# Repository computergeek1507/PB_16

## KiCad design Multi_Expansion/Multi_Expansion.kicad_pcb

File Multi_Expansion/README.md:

# Copyright and Disclaimer
Copyright: Scott Hanson

This documentation describes Open Hardware and is licensed under the CERN Open Hardware License Version 2 - Strongly Reciprocal. (CERN-OHL-S)

You may redistribute and modify this documentation under the terms of the CERN OHL-S-v2 (https://ohwr.org/cern_ohl_s_v2.txt). This documentation is distributed WITHOUT ANY EXPRESS OR IMPLIED WARRANTY, INCLUDING OF MERCHANTABILITY, SATISFACTORY QUALITY AND FITNESS FOR A PARTICULAR PURPOSE. Please see the CERN OHL v2-S for applicable conditions

**Under CERN OHL-S-v2, derivative work must be publicly released as defined in subsection 3.3**

# Multi Expansion

The Multi Expansion is a dual Differental Reciever output board with eight local pixel outputs for the PB16. It works with Smart and Dumb Differental Recievers. All the design files are open source and available on github.

## [Part BOM](https://github.com/computergeek1507/PB_16/raw/master/Multi_Expansion/Multi_Expansion.ods)

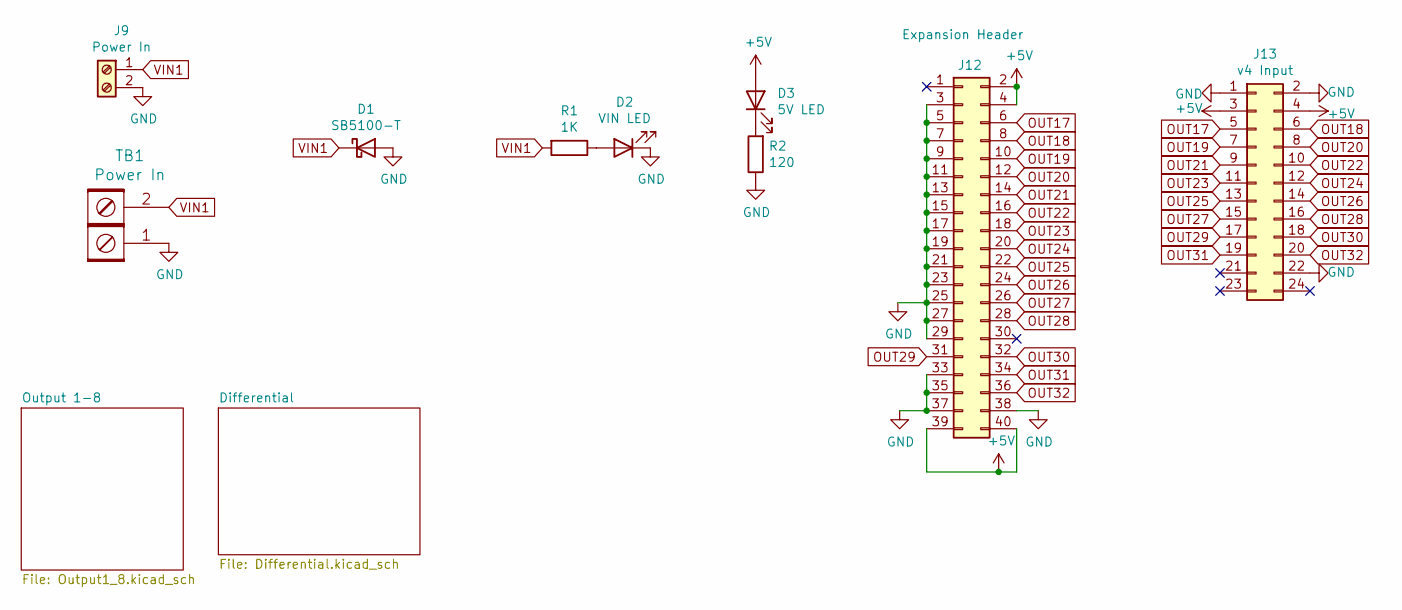
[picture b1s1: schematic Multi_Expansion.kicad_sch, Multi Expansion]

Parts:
D1: SB5100-T; D_DO-201AD_P12.70mm_Horizontal; MPN SB5100-T; Digi-Key_PN SB5100DICT-ND
D2: VIN LED; LED_D3.0mm_Clear; MPN WP3A8GD; Digi-Key_PN 754-1217-ND
D3: 5V LED; LED_D3.0mm_Clear; MPN WP3A8GD; Digi-Key_PN 754-1217-ND
J9: Power In; TerminalBlock_MetzConnect_Type701_RT11L02HGLU_1x02_P6.35mm_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; Digi-Key_PN ED2675-ND
J12: Expansion Header; IDC-Header_2x20_P2.54mm_Vertical; MPN SBH11-PBPC-D20-ST-BK; Digi-Key_PN S9175-ND
J13: v4 Input; OST_302-S241; MPN 302-S241; Digi-Key_PN ED10525-ND
R1: 1K; R_Axial_DIN0207_L6.3mm_D2.5mm_P7.62mm_Horizontal; MPN CF14JT1K00; Digi-Key_PN CF14JT1K00CT-ND
R2: 120; R_Axial_DIN0207_L6.3mm_D2.5mm_P7.62mm_Horizontal; MPN CF14JT120R; Digi-Key_PN CF14JT120RCT-ND
TB1: Power In; BARRIER_BLOCK_1ROW_2POS_P9.5MM; Digi-Key_PN ED2953-ND

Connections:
+5V: D3.2 (A), J12.2, J12.4, J12.39, J12.40, J13.3, J13.4; also elsewhere on the board
GND: D1.2 (A), D2.1 (K), J9.2, J12.3, J12.5, J12.7, J12.9, J12.11, J12.13, J12.15, J12.17, J12.19, J12.21, J12.23, J12.25, J12.27, J12.29, J12.33, J12.35, J12.37, J12.38, J13.1, J13.2, J13.22, R2.1, TB1.1; also elsewhere on the board
unnamed: D2.2 (A), R1.1
unnamed: D3.1 (K), R2.2
OUT17: J12.6, J13.5; also elsewhere on the board
OUT18: J12.8, J13.6; also elsewhere on the board
OUT19: J12.10, J13.7; also elsewhere on the board
OUT20: J12.12, J13.8; also elsewhere on the board
OUT21: J12.14, J13.9; also elsewhere on the board
OUT22: J12.16, J13.10; also elsewhere on the board
OUT23: J12.18, J13.11; also elsewhere on the board
OUT24: J12.20, J13.12; also elsewhere on the board
OUT25: J12.22, J13.13; also elsewhere on the board
OUT26: J12.24, J13.14; also elsewhere on the board
OUT27: J12.26, J13.15; also elsewhere on the board
OUT28: J12.28, J13.16; also elsewhere on the board
OUT29: J12.31, J13.17; also elsewhere on the board
OUT30: J12.32, J13.18; also elsewhere on the board
OUT31: J12.34, J13.19; also elsewhere on the board
OUT32: J12.36, J13.20; also elsewhere on the board
VIN1: D1.1 (K), J9.1, R1.2, TB1.2; also elsewhere on the board

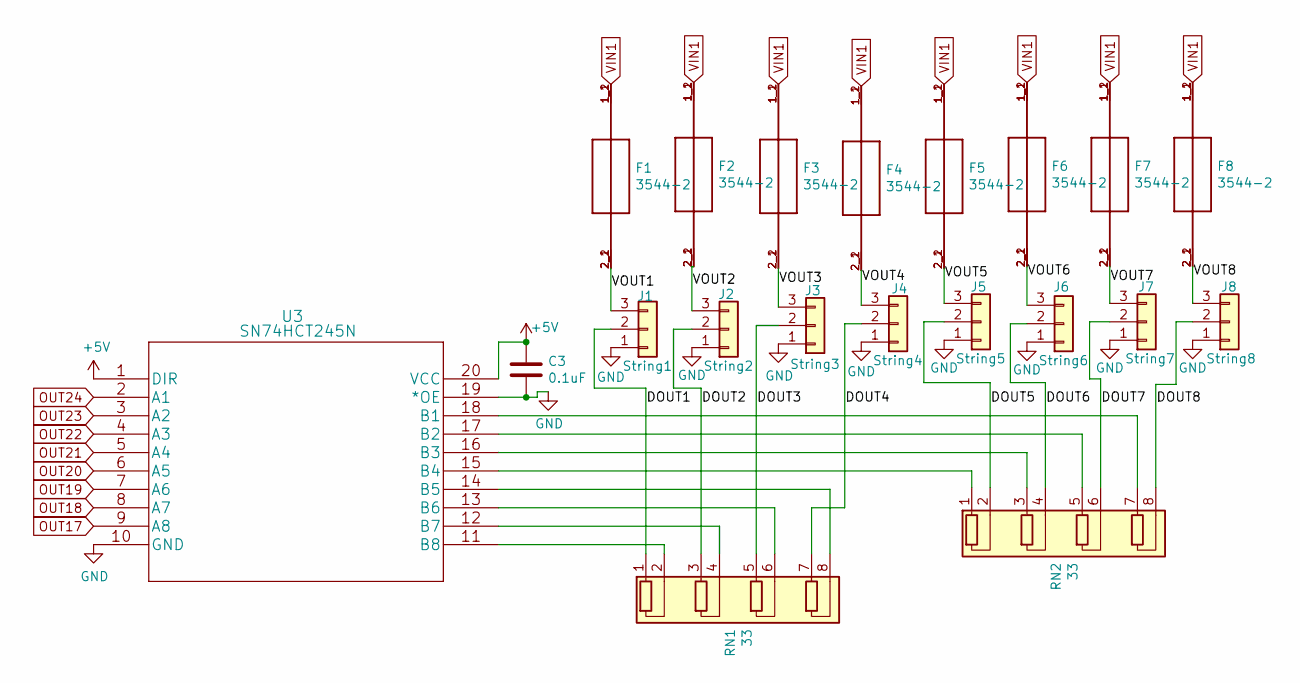
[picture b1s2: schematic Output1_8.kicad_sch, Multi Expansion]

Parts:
C3: 0.1uF; C_Rect_L7.0mm_W2.0mm_P5.00mm; MPN SR215C104KARTR1; Digi-Key_PN 478-7336-1-ND
F1, F2, F3, F4, F5, F6, F7, F8: 3544-2; FUSE_3544-2; MPN 3544-2; Digi-Key_PN 36-3544-2-ND
J1: String1; PhoenixContact_MCV_1,5_3-G-3.5_1x03_P3.50mm_Vertical; MPN 1843619/OSTTJ0311530; Digi-Key_PN 277-5737-ND/ED10555-ND
J2: String2; PhoenixContact_MCV_1,5_3-G-3.5_1x03_P3.50mm_Vertical; MPN 1843619/OSTTJ0311530; Digi-Key_PN 277-5737-ND/ED10555-ND
J3: String3; PhoenixContact_MCV_1,5_3-G-3.5_1x03_P3.50mm_Vertical; MPN 1843619/OSTTJ0311530; Digi-Key_PN 277-5737-ND/ED10555-ND
J4: String4; PhoenixContact_MCV_1,5_3-G-3.5_1x03_P3.50mm_Vertical; MPN 1843619/OSTTJ0311530; Digi-Key_PN 277-5737-ND/ED10555-ND
J5: String5; PhoenixContact_MCV_1,5_3-G-3.5_1x03_P3.50mm_Vertical; MPN 1843619/OSTTJ0311530; Digi-Key_PN 277-5737-ND/ED10555-ND
J6: String6; PhoenixContact_MCV_1,5_3-G-3.5_1x03_P3.50mm_Vertical; MPN 1843619/OSTTJ0311530; Digi-Key_PN 277-5737-ND/ED10555-ND
J7: String7; PhoenixContact_MCV_1,5_3-G-3.5_1x03_P3.50mm_Vertical; MPN 1843619/OSTTJ0311530; Digi-Key_PN 277-5737-ND/ED10555-ND
J8: String8; PhoenixContact_MCV_1,5_3-G-3.5_1x03_P3.50mm_Vertical; MPN 1843619/OSTTJ0311530; Digi-Key_PN 277-5737-ND/ED10555-ND
RN1, RN2: 33; R_Array_SIP8; MPN 4608X-102-330LF; Digi-Key_PN 4608X-2-330LF-ND
U3: SN74HCT245N; MPN SN74HCT245N; Digi-Key_PN 296-1612-5-ND

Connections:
+5V: C3.1, U3.1 (DIR), U3.20 (VCC); also elsewhere on the board
/Output 1-8/DOUT1: J1.2, RN1.1 (R1.1)
/Output 1-8/DOUT2: J2.2, RN1.3 (R2.1)
/Output 1-8/DOUT3: J3.2, RN1.5 (R3.1)
/Output 1-8/DOUT4: J4.2, RN1.7 (R4.1)
/Output 1-8/DOUT5: J5.2, RN2.2 (R1.2)
/Output 1-8/DOUT6: J6.2, RN2.4 (R2.2)
/Output 1-8/DOUT7: J7.2, RN2.6 (R3.2)
/Output 1-8/DOUT8: J8.2, RN2.8 (R4.2)
/Output 1-8/VOUT1: F1.2_1 (2), F1.2_2 (2), J1.3
/Output 1-8/VOUT2: F2.2_1 (2), F2.2_2 (2), J2.3
/Output 1-8/VOUT3: F3.2_1 (2), F3.2_2 (2), J3.3
/Output 1-8/VOUT4: F4.2_1 (2), F4.2_2 (2), J4.3
/Output 1-8/VOUT5: F5.2_1 (2), F5.2_2 (2), J5.3
/Output 1-8/VOUT6: F6.2_1 (2), F6.2_2 (2), J6.3
/Output 1-8/VOUT7: F7.2_1 (2), F7.2_2 (2), J7.3
/Output 1-8/VOUT8: F8.2_1 (2), F8.2_2 (2), J8.3
GND: C3.2, J1.1, J2.1, J3.1, J4.1, J5.1, J6.1, J7.1, J8.1, U3.10 (GND), U3.19 (*OE); also elsewhere on the board
unnamed: RN1.2 (R1.2), U3.11 (B8)
unnamed: RN1.4 (R2.2), U3.12 (B7)
unnamed: RN1.6 (R3.2), U3.13 (B6)
unnamed: RN1.8 (R4.2), U3.14 (B5)
unnamed: RN2.1 (R1.1), U3.15 (B4)
unnamed: RN2.3 (R2.1), U3.16 (B3)
unnamed: RN2.5 (R3.1), U3.17 (B2)
unnamed: RN2.7 (R4.1), U3.18 (B1)
OUT17: U3.9 (A8); also elsewhere on the board
OUT18: U3.8 (A7); also elsewhere on the board
OUT19: U3.7 (A6); also elsewhere on the board
OUT20: U3.6 (A5); also elsewhere on the board
OUT21: U3.5 (A4); also elsewhere on the board
OUT22: U3.4 (A3); also elsewhere on the board
OUT23: U3.3 (A2); also elsewhere on the board
OUT24: U3.2 (A1); also elsewhere on the board
VIN1: F1.1_1 (1), F1.1_2 (1), F2.1_1 (1), F2.1_2 (1), F3.1_1 (1), F3.1_2 (1), F4.1_1 (1), F4.1_2 (1), F5.1_1 (1), F5.1_2 (1), F6.1_1 (1), F6.1_2 (1), F7.1_1 (1), F7.1_2 (1), F8.1_1 (1), F8.1_2 (1); also elsewhere on the board

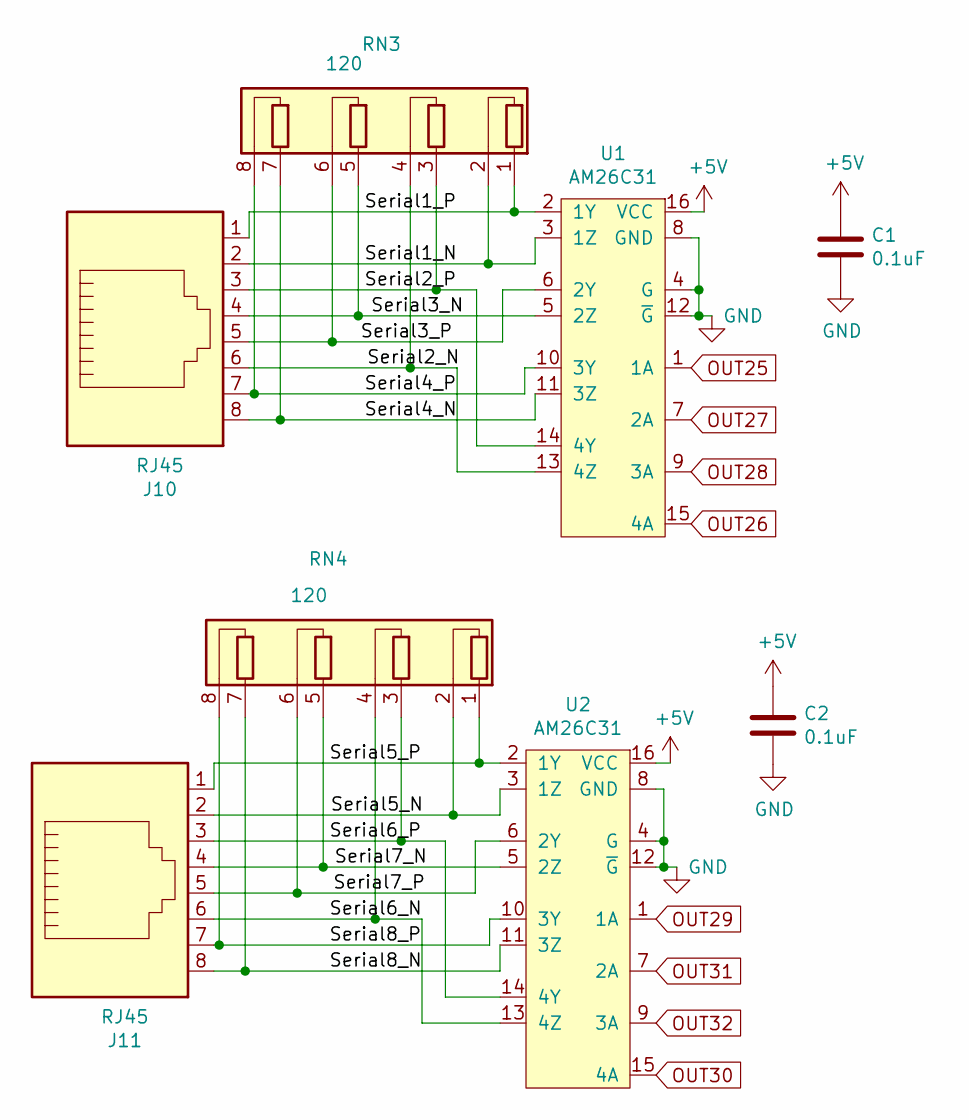
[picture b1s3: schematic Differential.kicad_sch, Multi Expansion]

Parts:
C1, C2: 0.1uF; C_Rect_L7.0mm_W2.0mm_P5.00mm; MPN SR215C104KARTR1; Digi-Key_PN 478-7336-1-ND
J10, J11: RJ45; RJ45_Amphenol_54602-x08_Horizontal; Digi-Key_PN AE10392-ND
RN3, RN4: 120; R_Array_SIP8; Digi-Key_PN 4608X-2-121LF-ND
U1, U2: AM26C31; DIP-16_W7.62mm; Farnell 4975637

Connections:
+5V: C1.1, C2.1, U1.16 (VCC), U2.16 (VCC); also elsewhere on the board
/Differential/Serial1_N: J10.2, RN3.2 (R1.2), U1.3 (1Z)
/Differential/Serial1_P: J10.1, RN3.1 (R1.1), U1.2 (1Y)
/Differential/Serial2_N: J10.6, RN3.4 (R2.2), U1.13 (4Z)
/Differential/Serial2_P: J10.3, RN3.3 (R2.1), U1.14 (4Y)
/Differential/Serial3_N: J10.4, RN3.5 (R3.1), U1.5 (2Z)
/Differential/Serial3_P: J10.5, RN3.6 (R3.2), U1.6 (2Y)
/Differential/Serial4_N: J10.8, RN3.7 (R4.1), U1.11 (3Z)
/Differential/Serial4_P: J10.7, RN3.8 (R4.2), U1.10 (3Y)
/Differential/Serial5_N: J11.2, RN4.2 (R1.2), U2.3 (1Z)
/Differential/Serial5_P: J11.1, RN4.1 (R1.1), U2.2 (1Y)
/Differential/Serial6_N: J11.6, RN4.4 (R2.2), U2.13 (4Z)
/Differential/Serial6_P: J11.3, RN4.3 (R2.1), U2.14 (4Y)
/Differential/Serial7_N: J11.4, RN4.5 (R3.1), U2.5 (2Z)
/Differential/Serial7_P: J11.5, RN4.6 (R3.2), U2.6 (2Y)
/Differential/Serial8_N: J11.8, RN4.7 (R4.1), U2.11 (3Z)
/Differential/Serial8_P: J11.7, RN4.8 (R4.2), U2.10 (3Y)
GND: C1.2, C2.2, U1.4 (G), U1.8 (GND), U1.12 (~G), U2.4 (G), U2.8 (GND), U2.12 (~G); also elsewhere on the board
OUT25: U1.1 (1A); also elsewhere on the board
OUT26: U1.15 (4A); also elsewhere on the board
OUT27: U1.7 (2A); also elsewhere on the board
OUT28: U1.9 (3A); also elsewhere on the board
OUT29: U2.1 (1A); also elsewhere on the board
OUT30: U2.15 (4A); also elsewhere on the board
OUT31: U2.7 (2A); also elsewhere on the board
OUT32: U2.9 (3A); also elsewhere on the board

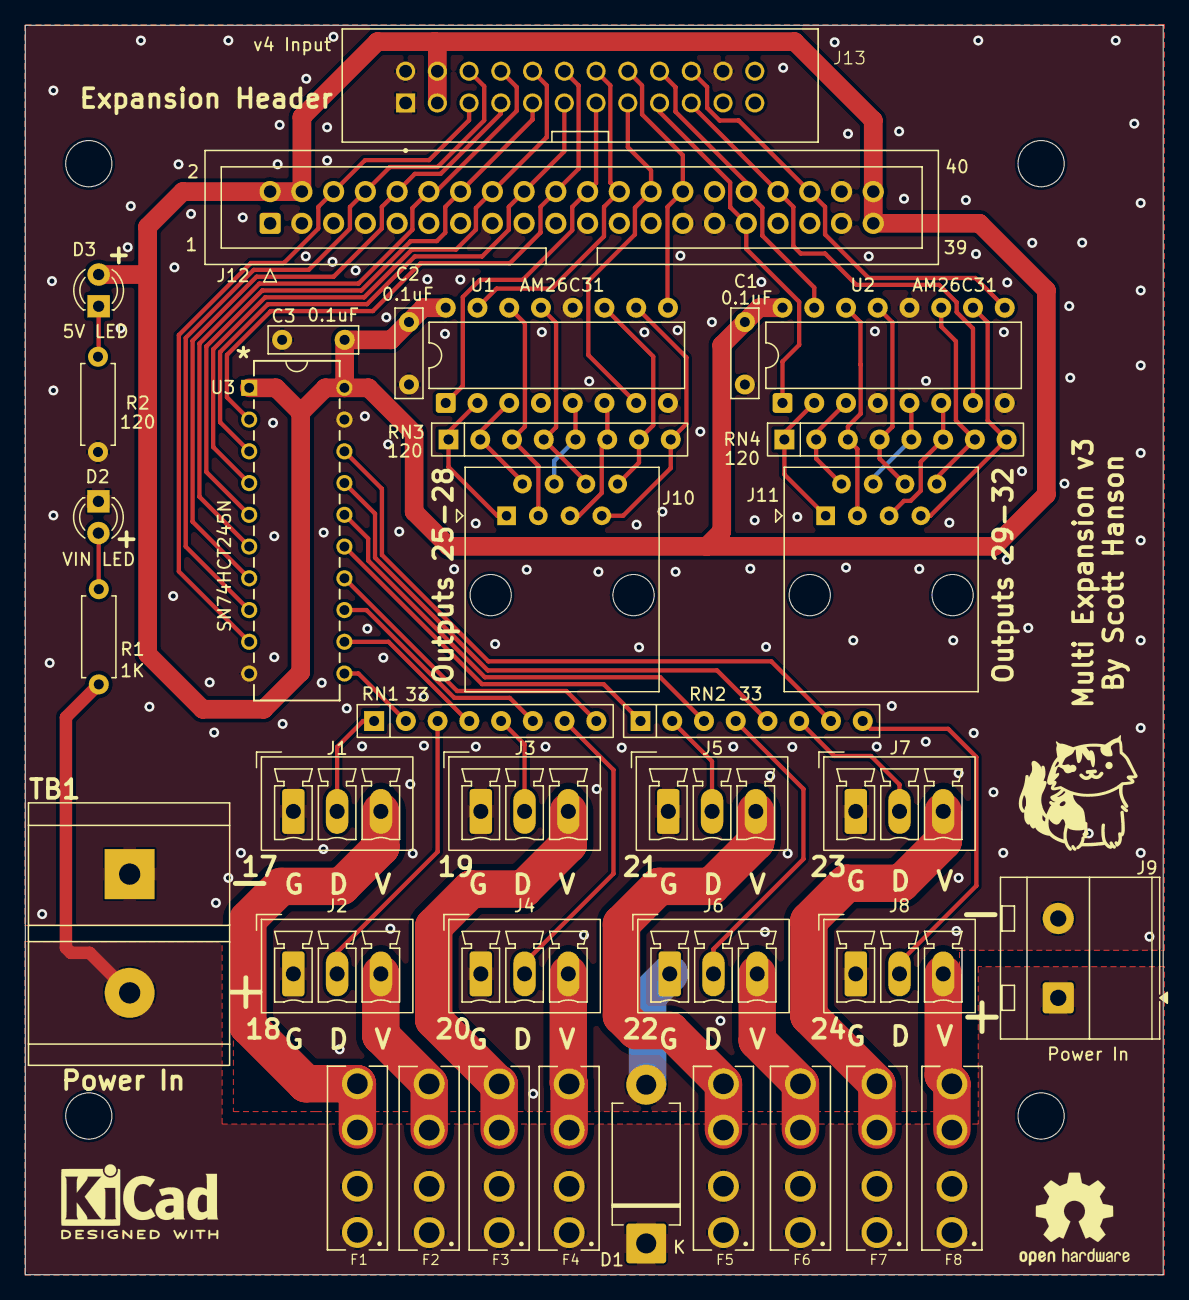
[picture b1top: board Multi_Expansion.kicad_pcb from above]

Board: 2 copper layers, 91.0 x 100.0 mm, 37 parts (0 on the bottom side), 61 nets.

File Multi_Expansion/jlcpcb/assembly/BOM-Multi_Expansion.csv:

Comment,Designator,Footprint,LCSC
String2,J2,"PhoenixContact_MCV_1,5_3-G-3.5_1x03_P3.50mm_Vertical",
String5,J5,"PhoenixContact_MCV_1,5_3-G-3.5_1x03_P3.50mm_Vertical",
String6,J6,"PhoenixContact_MCV_1,5_3-G-3.5_1x03_P3.50mm_Vertical",
String7,J7,"PhoenixContact_MCV_1,5_3-G-3.5_1x03_P3.50mm_Vertical",
String8,J8,"PhoenixContact_MCV_1,5_3-G-3.5_1x03_P3.50mm_Vertical",
3544-2,F1,FUSE_3544-2,
3544-2,F7,FUSE_3544-2,
0.1uF,C3,C_Rect_L7.0mm_W2.0mm_P5.00mm,
3544-2,F2,FUSE_3544-2,
3544-2,F6,FUSE_3544-2,
3544-2,F8,FUSE_3544-2,
3544-2,F5,FUSE_3544-2,
3544-2,F3,FUSE_3544-2,
33,RN1,R_Array_SIP8,
3544-2,F4,FUSE_3544-2,
String1,J1,"PhoenixContact_MCV_1,5_3-G-3.5_1x03_P3.50mm_Vertical",
String3,J3,"PhoenixContact_MCV_1,5_3-G-3.5_1x03_P3.50mm_Vertical",
String4,J4,"PhoenixContact_MCV_1,5_3-G-3.5_1x03_P3.50mm_Vertical",
SB5100-T,D1,D_DO-201AD_P12.70mm_Horizontal,
1K,R1,R_Axial_DIN0207_L6.3mm_D2.5mm_P7.62mm_Horizontal,
5V LED,D3,LED_D3.0mm_Clear,
120,R2,R_Axial_DIN0207_L6.3mm_D2.5mm_P7.62mm_Horizontal,
SN74HCT245N,U3,SN74HCT245N,
33,RN2,R_Array_SIP8,
Power In,TB1,BARRIER_BLOCK_1ROW_2POS_P9.5MM,
VIN LED,D2,LED_D3.0mm_Clear,
AM26C31,U1,DIP-16_W7.62mm,
0.1uF,C2,C_Rect_L7.0mm_W2.0mm_P5.00mm,
0.1uF,C1,C_Rect_L7.0mm_W2.0mm_P5.00mm,
AM26C31,U2,DIP-16_W7.62mm,
120,RN3,R_Array_SIP8,
120,RN4,R_Array_SIP8,
RJ45,J11,RJ45_Amphenol_54602-x08_Horizontal,
RJ45,J10,RJ45_Amphenol_54602-x08_Horizontal,
Power In,J9,TerminalBlock_MetzConnect_Type701_RT11L02HGLU_1x02_P6.35mm_Horizontal,
Expansion Header,J12,IDC-Header_2x20_P2.54mm_Vertical,
v4 Input,J13,OST_302-S241,

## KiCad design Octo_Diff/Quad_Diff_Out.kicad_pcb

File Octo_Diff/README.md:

# Copyright and Disclaimer
Copyright: Scott Hanson

This documentation describes Open Hardware and is licensed under the CERN Open Hardware License Version 2 - Strongly Reciprocal. (CERN-OHL-S)

You may redistribute and modify this documentation under the terms of the CERN OHL-S-v2 (https://ohwr.org/cern_ohl_s_v2.txt). This documentation is distributed WITHOUT ANY EXPRESS OR IMPLIED WARRANTY, INCLUDING OF MERCHANTABILITY, SATISFACTORY QUALITY AND FITNESS FOR A PARTICULAR PURPOSE. Please see the CERN OHL v2-S for applicable conditions

**Under CERN OHL-S-v2, derivative work must be publicly released as defined in subsection 3.3**

# Octo Diff Out

The Octo Diff Out is a dual Differental Reciever output board for the PB16. It works with Smart and Dumb Differental Recievers. All the design files are open source and available on github.

## [Part BOM](https://github.com/computergeek1507/PB_16/raw/master/Octo_Diff/Octo_Diff_BOM.ods)

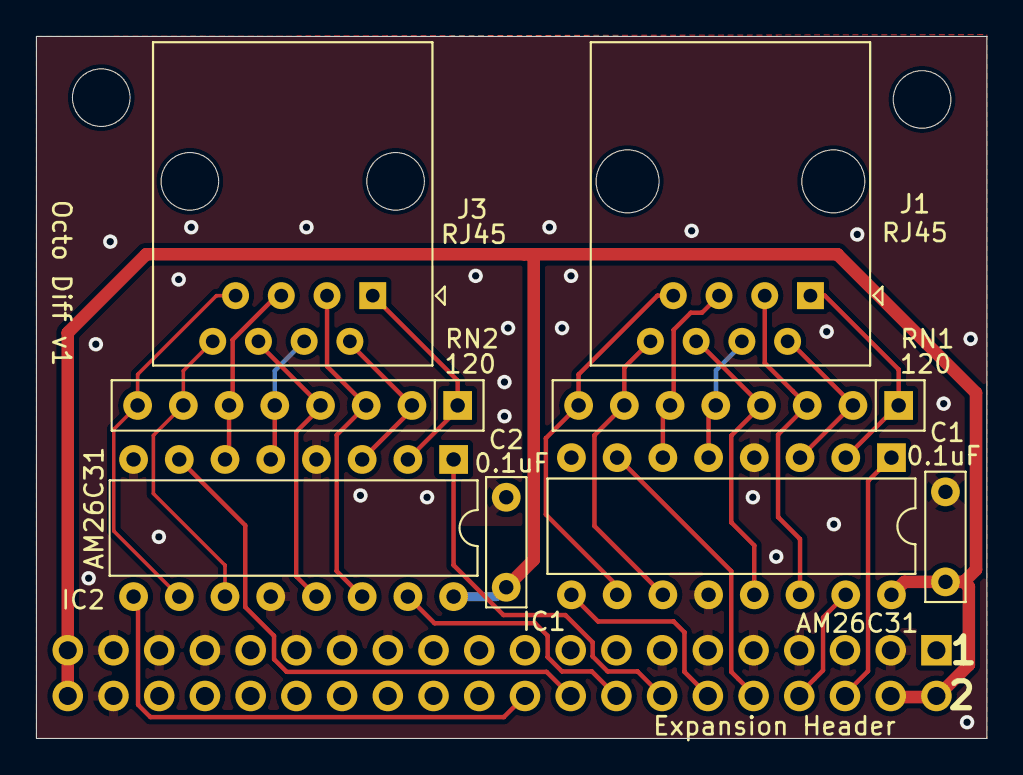
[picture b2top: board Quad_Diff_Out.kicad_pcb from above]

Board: 2 copper layers, 52.8 x 39.0 mm, 11 parts (1 on the bottom side), 26 nets.

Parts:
C1, C2: 0.1uF; C_Rect_L7.0mm_W2.0mm_P5.00mm
H1, H2: MountingHole; MountingHole_3.2mm_M3
IC1, IC2: AM26C31; DIP-16_W7.62mm
J1, J3: RJ45; RJ45_Amphenol_54602-x08_Horizontal
J2: Expansion Header; PinSocket_2x20_P2.54mm_Vertical
RN1, RN2: 120; R_Array_SIP8

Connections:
+5V: C1.1, C2.1, IC1.16 (VCC), IC2.16 (VCC), J2.2, J2.4, J2.39, J2.40
/DATA17: IC1.1 (1A), J2.6
/DATA18: IC1.15 (4A), J2.8
/DATA19: IC1.7 (2A), J2.10
/DATA20: IC1.9 (3A), J2.12
/DATA21: IC2.1 (1A), J2.14
/DATA22: IC2.15 (4A), J2.16
/DATA23: IC2.7 (2A), J2.18
/DATA24: IC2.9 (3A), J2.20
/Serial1_N: IC1.3 (1Z), J1.2, RN1.2 (R1.2)
/Serial1_P: IC1.2 (1Y), J1.1, RN1.1 (R1.1)
/Serial2_N: IC1.13 (4Z), J1.6, RN1.4 (R2.2)
/Serial2_P: IC1.14 (4Y), J1.3, RN1.3 (R2.1)
/Serial3_N: IC1.5 (2Z), J1.4, RN1.5 (R3.1)
/Serial3_P: IC1.6 (2Y), J1.5, RN1.6 (R3.2)
/Serial4_N: IC1.11 (3Z), J1.8, RN1.7 (R4.1)
/Serial4_P: IC1.10 (3Y), J1.7, RN1.8 (R4.2)
/Serial5_N: IC2.5 (2Z), J3.4, RN2.5 (R3.1)
/Serial6_N: IC2.13 (4Z), J3.6, RN2.4 (R2.2)
/Serial7_P: IC2.6 (2Y), J3.5, RN2.6 (R3.2)
/Serial8_N: IC2.11 (3Z), J3.8, RN2.7 (R4.1)
/Serial8_P: IC2.10 (3Y), J3.7, RN2.8 (R4.2)
GND: C1.2, C2.2, IC1.4 (G), IC1.8 (GND), IC1.12 (~G), IC2.4 (G), IC2.8 (GND), IC2.12 (~G), J2.3, J2.5, J2.7, J2.9, J2.11, J2.13, J2.15, J2.17, J2.19, J2.21, J2.23, J2.25, J2.27, J2.29, J2.33, J2.35, J2.37, J2.38
unnamed: IC2.2 (1Y), J3.1, RN2.1 (R1.1)
unnamed: IC2.3 (1Z), J3.2, RN2.2 (R1.2)
unnamed: IC2.14 (4Y), J3.3, RN2.3 (R2.1)

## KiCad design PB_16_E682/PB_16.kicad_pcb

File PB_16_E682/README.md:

# Copyright and Disclaimer
Copyright: Scott Hanson

This documentation describes Open Hardware and is licensed under the CERN Open Hardware License Version 2 - Strongly Reciprocal. (CERN-OHL-S)

You may redistribute and modify this documentation under the terms of the CERN OHL-S-v2 (https://ohwr.org/cern_ohl_s_v2.txt). This documentation is distributed WITHOUT ANY EXPRESS OR IMPLIED WARRANTY, INCLUDING OF MERCHANTABILITY, SATISFACTORY QUALITY AND FITNESS FOR A PARTICULAR PURPOSE. Please see the CERN OHL v2-S for applicable conditions

**Under CERN OHL-S-v2, derivative work must be publicly released as defined in subsection 3.3**

# PB 16 E682

**This is a proof of concept, not designed for extended use**

The PB16 E682 is an "Upgrade" for the Sandevice E682. The E682's Parallax Propeller microcontroller is replaced with a PocketBeagle runnig FPP. It runs a full Linux operating system with ethernet, WIFI and audio supported over the USB port. The PCB is powered by the Aux Power Connector J17 5V out from the E682. It can run in standalone, or be used with other controllers/devices. There is also an optional [serial breakout board](../PB_16_E682_Serial/README.md) for DMX capability. All the design files are open source and available on github.

## [Part BOM](https://github.com/computergeek1507/PB_16/raw/master/PB_16_E682/PB_16_E682_BOM.ods)

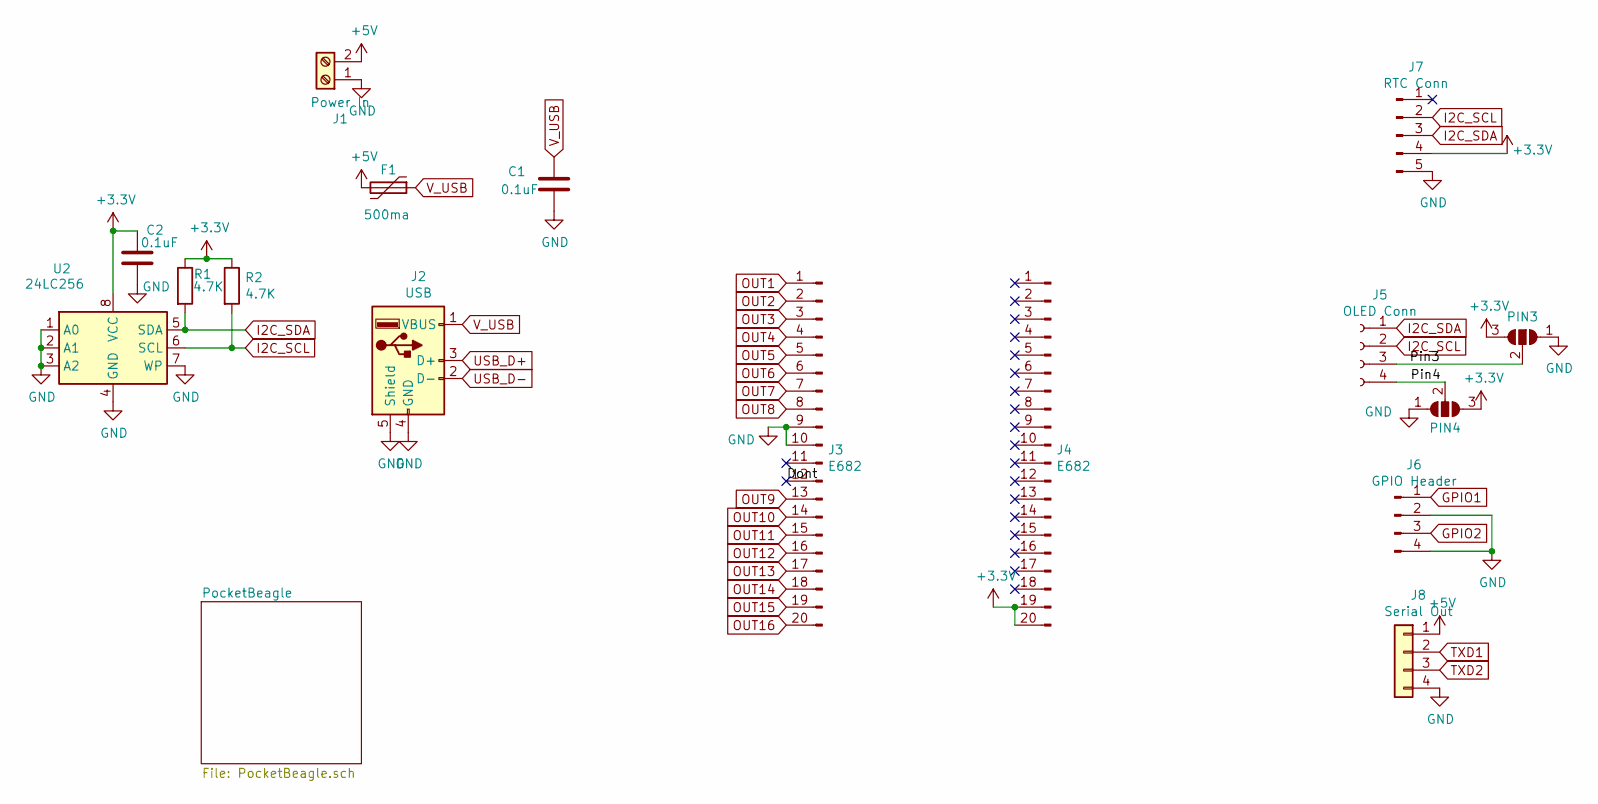
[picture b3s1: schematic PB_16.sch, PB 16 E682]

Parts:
C1, C2: 0.1uF; C_Rect_L7.0mm_W2.0mm_P5.00mm; MPN SR215C104KARTR1; Digi-Key_PN 478-7336-1-ND
F1: 500ma; Fuse_BelFuse_0ZRE0005FF_L8.3mm_W3.8mm; MPN RXEF050-2; Digi-Key_PN RXEF050-2HFCT-ND
J1: Power In; PHOENIX_MKDS1%2f2-3.81; MPN 1727010; Digi-Key_PN 277-1947-ND
J2: USB; USB_A_Molex_105057_Vertical; MPN 1050570001; Digi-Key_PN WM8672-ND
J3, J4: E682; PinHeader_1x20_P2.54mm_Vertical; MPN 61302011121; Digi-Key_PN 732-5329-ND
J5: OLED Conn; PinSocket_1x04_P2.54mm_Vertical; MPN PPTC041LFBN-RC; Digi-Key_PN S7002-ND
J6: GPIO Header; JST_XH_B4B-XH-A_1x04_P2.50mm_Vertical; MPN B4B-XH-A(LF)(SN); Digi-Key_PN 455-2249-ND
J7: RTC Conn; PinHeader_1x05_P2.54mm_Vertical; MPN 61300511121; Digi-Key_PN 732-5318-ND
J8: Serial Out; PinHeader_1x04_P2.54mm_Vertical; MPN 61300411121; Digi-Key_PN 732-5317-ND
PIN3, PIN4: SolderJumper_3_Open; SolderJumper-3_P1.3mm_Open_Pad1.0x1.5mm
R1, R2: 4.7K; R_Axial_DIN0207_L6.3mm_D2.5mm_P7.62mm_Horizontal; MPN CF14JT4K70; Digi-Key_PN CF14JT4K70CT-ND
U2: 24LC256; DIP-8_W7.62mm; MPN FT24C256A-UDR-B; Digi-Key_PN 1219-1052-ND

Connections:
+3V3: C2.1, J4.19, J4.20, J7.4, PIN3.3 (B), PIN4.3 (B), R1.1, R2.1, U2.8 (VCC); also elsewhere on the board
+5V: F1.2, J1.2, J8.1; also elsewhere on the board
/Dont: J3.12
/Pin3: J5.3, PIN3.2 (C)
/Pin4: J5.4, PIN4.2 (C)
GND: C1.2, C2.2, J1.1, J2.4 (GND), J2.5 (Shield), J3.9, J3.10, J6.2, J6.4, J7.5, J8.4, PIN3.1 (A), PIN4.1 (A), U2.1 (A0), U2.2 (A1), U2.3 (A2), U2.4 (GND), U2.7 (WP); also elsewhere on the board
GPIO1: J6.1; also elsewhere on the board
GPIO2: J6.3; also elsewhere on the board
I2C_SCL: J5.2, J7.2, R2.2, U2.6 (SCL); also elsewhere on the board
I2C_SDA: J5.1, J7.3, R1.2, U2.5 (SDA); also elsewhere on the board
OUT1: J3.1; also elsewhere on the board
OUT2: J3.2; also elsewhere on the board
OUT3: J3.3; also elsewhere on the board
OUT4: J3.4; also elsewhere on the board
OUT5: J3.5; also elsewhere on the board
OUT6: J3.6; also elsewhere on the board
OUT7: J3.7; also elsewhere on the board
OUT8: J3.8; also elsewhere on the board
OUT9: J3.13; also elsewhere on the board
OUT10: J3.14; also elsewhere on the board
OUT11: J3.15; also elsewhere on the board
OUT12: J3.16; also elsewhere on the board
OUT13: J3.17; also elsewhere on the board
OUT14: J3.18; also elsewhere on the board
OUT15: J3.19; also elsewhere on the board
OUT16: J3.20; also elsewhere on the board
TXD1: J8.2; also elsewhere on the board
TXD2: J8.3; also elsewhere on the board
USB_D+: J2.3 (D+); also elsewhere on the board
USB_D-: J2.2 (D-); also elsewhere on the board
V_USB: C1.1, F1.1, J2.1 (VBUS); also elsewhere on the board

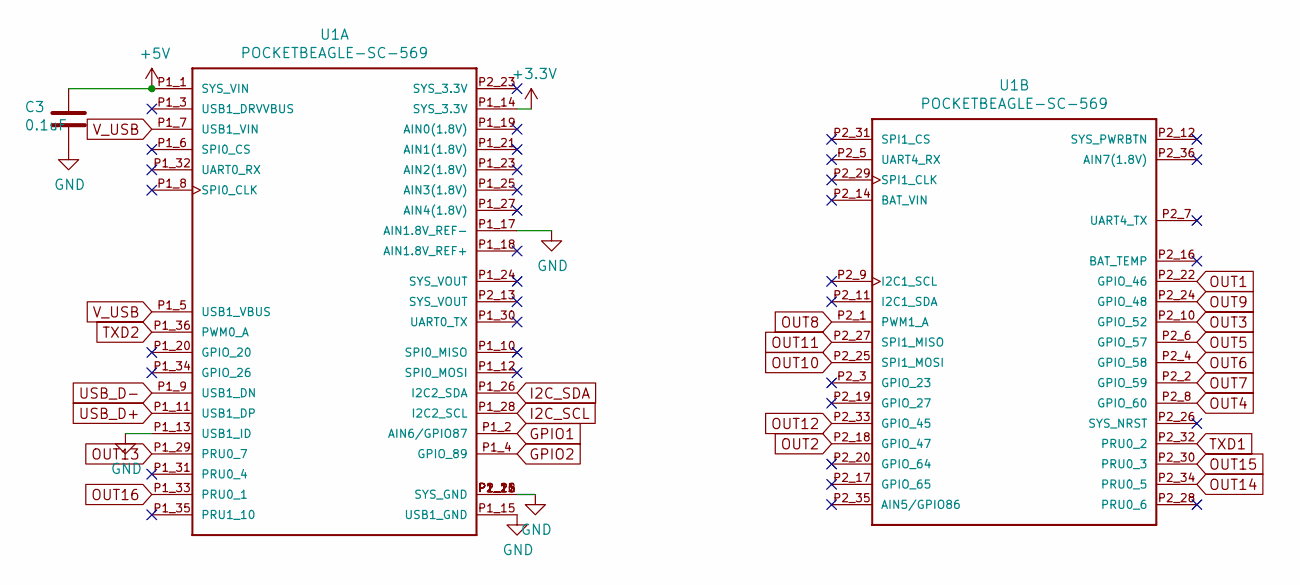
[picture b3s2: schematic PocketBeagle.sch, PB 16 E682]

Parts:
C3: 0.1uF; C_Rect_L7.0mm_W2.0mm_P5.00mm; MPN SR215C104KARTR1; Digi-Key_PN 478-7336-1-ND
U1: POCKETBEAGLE-SC-569; BEAGLE_POCKETBEAGLE-SC-569; MPN POCKETBEAGLE-SC-569; Digi-Key_PN POCKETBEAGLE-SC-569-ND

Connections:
+3V3: U1.P1_14 (SYS_3.3V); also elsewhere on the board
+5V: C3.1, U1.P1_1 (SYS_VIN); also elsewhere on the board
GND: C3.2, U1.P1_13 (USB1_ID), U1.P1_15 (USB1_GND), U1.P1_16 (SYS_GND), U1.P1_17 (AIN1.8V_REF-), U1.P1_22 (SYS_GND), U1.P2_15 (SYS_GND), U1.P2_21 (SYS_GND); also elsewhere on the board
GPIO1: U1.P1_2 (AIN6/GPIO87); also elsewhere on the board
GPIO2: U1.P1_4 (GPIO_89); also elsewhere on the board
I2C_SCL: U1.P1_28 (I2C2_SCL); also elsewhere on the board
I2C_SDA: U1.P1_26 (I2C2_SDA); also elsewhere on the board
OUT1: U1.P2_22 (GPIO_46); also elsewhere on the board
OUT2: U1.P2_18 (GPIO_47); also elsewhere on the board
OUT3: U1.P2_10 (GPIO_52); also elsewhere on the board
OUT4: U1.P2_8 (GPIO_60); also elsewhere on the board
OUT5: U1.P2_6 (GPIO_57); also elsewhere on the board
OUT6: U1.P2_4 (GPIO_58); also elsewhere on the board
OUT7: U1.P2_2 (GPIO_59); also elsewhere on the board
OUT8: U1.P2_1 (PWM1_A); also elsewhere on the board
OUT9: U1.P2_24 (GPIO_48); also elsewhere on the board
OUT10: U1.P2_25 (SPI1_MOSI); also elsewhere on the board
OUT11: U1.P2_27 (SPI1_MISO); also elsewhere on the board
OUT12: U1.P2_33 (GPIO_45); also elsewhere on the board
OUT13: U1.P1_29 (PRU0_7); also elsewhere on the board
OUT14: U1.P2_34 (PRU0_5); also elsewhere on the board
OUT15: U1.P2_30 (PRU0_3); also elsewhere on the board
OUT16: U1.P1_33 (PRU0_1); also elsewhere on the board
TXD1: U1.P2_32 (PRU0_2); also elsewhere on the board
TXD2: U1.P1_36 (PWM0_A); also elsewhere on the board
USB_D+: U1.P1_11 (USB1_DP); also elsewhere on the board
USB_D-: U1.P1_9 (USB1_DN); also elsewhere on the board
V_USB: U1.P1_5 (USB1_VBUS), U1.P1_7 (USB1_VIN); also elsewhere on the board

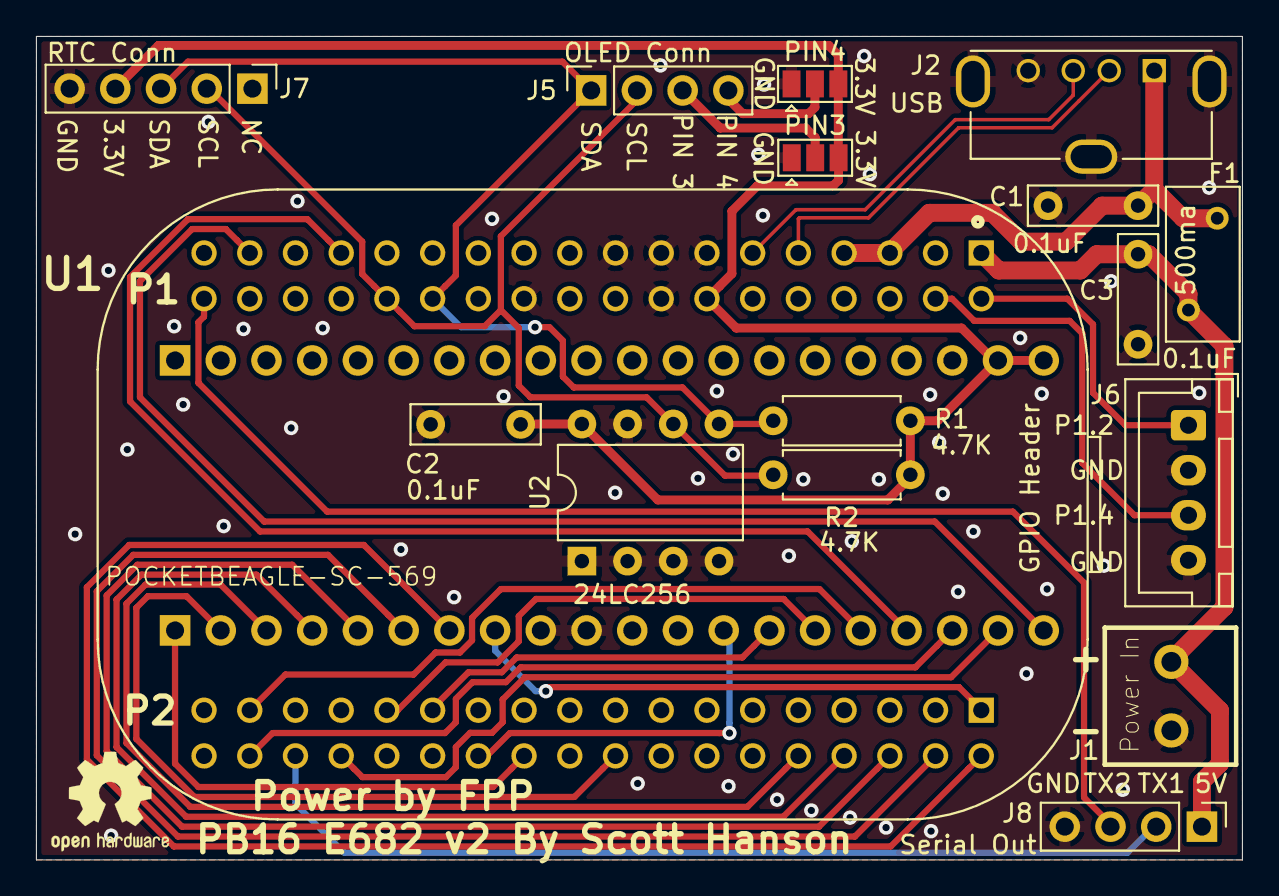
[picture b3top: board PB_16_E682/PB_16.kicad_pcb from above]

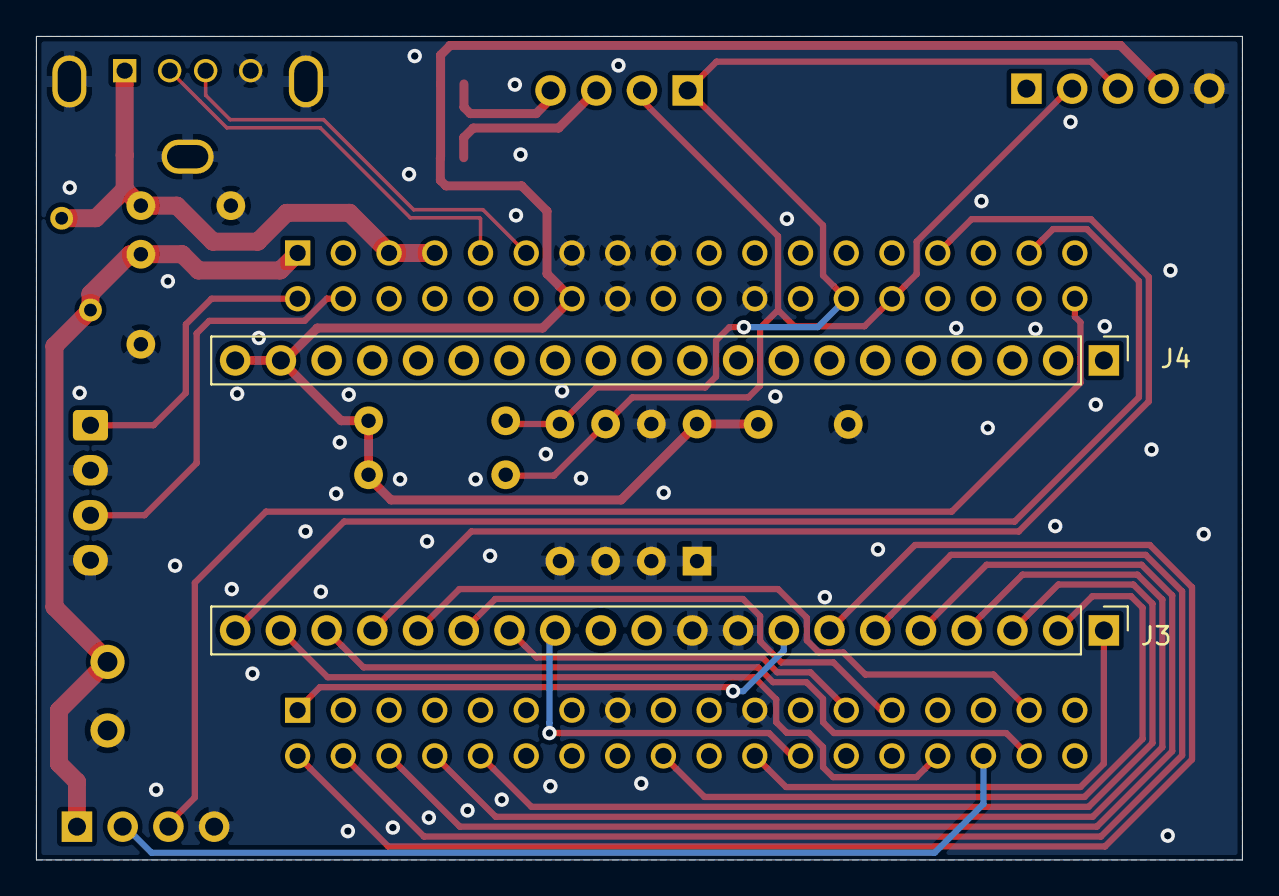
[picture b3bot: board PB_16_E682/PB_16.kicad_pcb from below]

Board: 2 copper layers, 67.0 x 45.8 mm, 18 parts (2 on the bottom side), 30 nets.

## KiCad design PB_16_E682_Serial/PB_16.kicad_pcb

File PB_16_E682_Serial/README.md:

# Copyright and Disclaimer
Copyright: Scott Hanson

This documentation describes Open Hardware and is licensed under the CERN Open Hardware License Version 2 - Strongly Reciprocal. (CERN-OHL-S)

You may redistribute and modify this documentation under the terms of the CERN OHL-S-v2 (https://ohwr.org/cern_ohl_s_v2.txt). This documentation is distributed WITHOUT ANY EXPRESS OR IMPLIED WARRANTY, INCLUDING OF MERCHANTABILITY, SATISFACTORY QUALITY AND FITNESS FOR A PARTICULAR PURPOSE. Please see the CERN OHL v2-S for applicable conditions

**Under CERN OHL-S-v2, derivative work must be publicly released as defined in subsection 3.3**

# PB 16 E682 Serial

The PB16 E682 Serial is the Serial breakout for the PB16 E682. The serial breakout board supports DMX protocol with DMX, LOR, and Renard pinouts. All the design files are open source and available on github.

## [Part BOM](https://github.com/computergeek1507/PB_16/raw/master/PB_16_E682_Serial/PB_16_E682_Serial_BOM.ods)

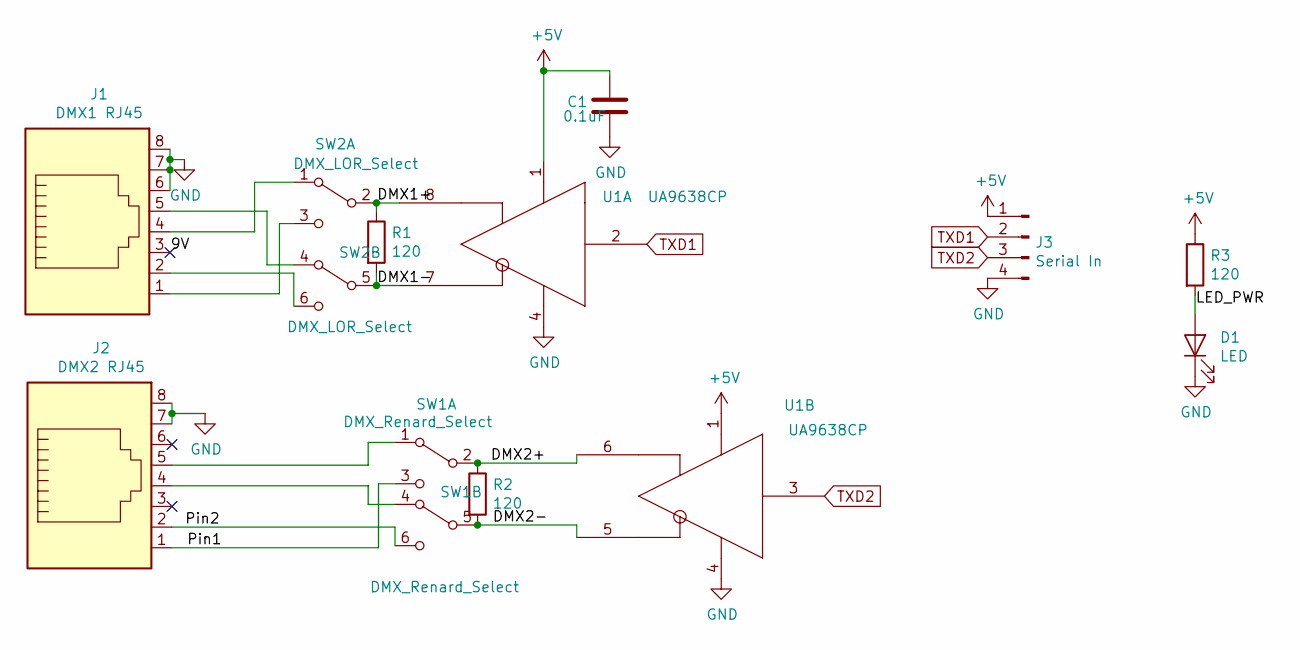
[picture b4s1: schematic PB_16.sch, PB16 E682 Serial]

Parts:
C1: 0.1uF; C_Rect_L7.0mm_W2.0mm_P5.00mm; MPN SR215C104KARTR1; Digi-Key_PN 478-7336-1-ND
D1: LED; LED_D3.0mm_Clear; MPN 151031VS06000; Digi-Key_PN 732-5008-ND
J1: DMX1 RJ45; RJ45_Amphenol_54602-x08_Horizontal; MPN A-2014-2-4-R; Digi-Key_PN AE10392-ND
J2: DMX2 RJ45; RJ45_Amphenol_54602-x08_Horizontal; MPN A-2014-2-4-R; Digi-Key_PN AE10392-ND
J3: Serial In; PinHeader_1x04_P2.54mm_Vertical; MPN 61300411121; Digi-Key_PN 732-5317-ND
R1, R2, R3: 120; R_Axial_DIN0207_L6.3mm_D2.5mm_P7.62mm_Horizontal; MPN CF14JT120R; Digi-Key_PN CF14JT120RCT-ND
SW1: DMX_Renard_Select; SW_CuK_JS202011CQN_DPDT_Straight; MPN JS202011CQN; Digi-Key_PN 401-2001-ND
SW2: DMX_LOR_Select; SW_CuK_JS202011CQN_DPDT_Straight; MPN JS202011CQN; Digi-Key_PN 401-2001-ND
U1: UA9638CP; DIP-8_W7.62mm; MPN UA9638CP; Digi-Key_PN 296-15059-5-ND

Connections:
+5V: C1.1, J3.1, R3.1, U1.1 (VCC)
/9V: J1.3
/DMX1+: R1.1, SW2.2 (B), U1.8 (OUTB)
/DMX1-: R1.2, SW2.5 (B), U1.7 (OUTA)
/DMX2+: R2.1, SW1.2 (B), U1.6 (OUTB)
/DMX2-: R2.2, SW1.5 (B), U1.5 (OUTA)
/LED_PWR: D1.2 (A), R3.2
/Pin1: J2.1, SW1.3 (C)
/Pin2: J2.2, SW1.6 (C)
GND: C1.2, D1.1 (K), J1.6, J1.7, J1.8, J2.7, J2.8, J3.4, U1.4 (GND)
unnamed: J1.1, SW2.3 (C)
unnamed: J1.2, SW2.6 (C)
unnamed: J1.4, SW2.1 (A)
unnamed: J1.5, SW2.4 (A)
unnamed: J2.4, SW1.4 (A)
unnamed: J2.5, SW1.1 (A)
TXD1: J3.2, U1.2 (IN)
TXD2: J3.3, U1.3 (IN)

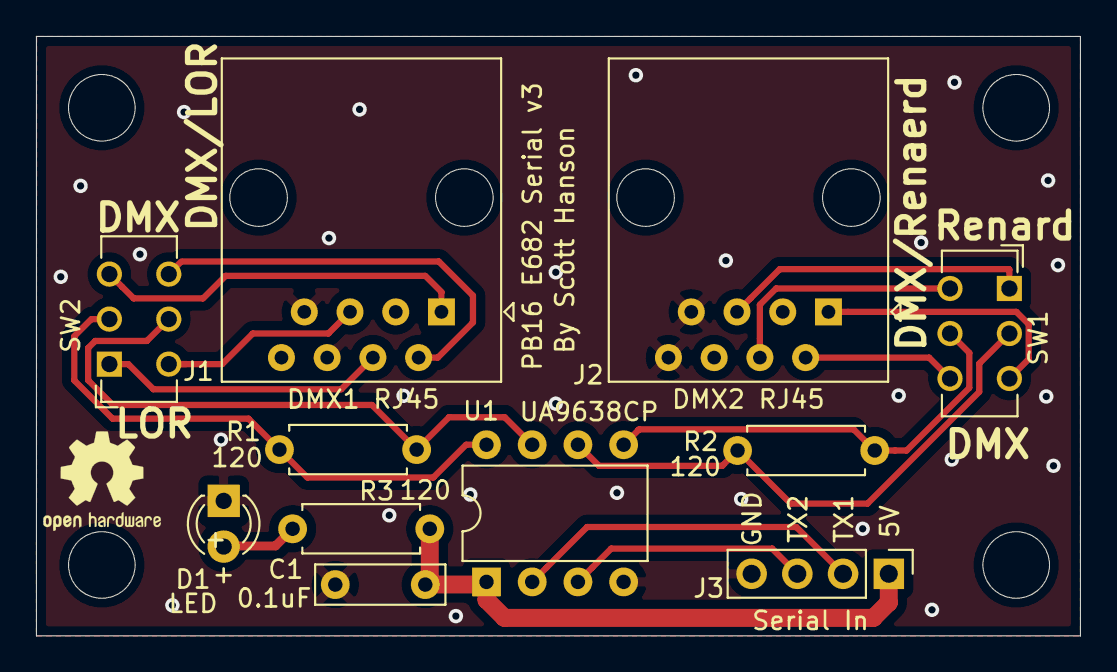
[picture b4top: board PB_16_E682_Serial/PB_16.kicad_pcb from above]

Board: 2 copper layers, 58.0 x 33.3 mm, 11 parts (0 on the bottom side), 17 nets.

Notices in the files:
parts and their libraries:
Copyright 2016 Accelerated Designs. All rights reserved.
